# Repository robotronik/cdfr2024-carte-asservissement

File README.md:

# Carte d'asservissement Robotronik CDFR 2024

Projet Kicad qui a pour but de faire l'asservissement de la base roulante.

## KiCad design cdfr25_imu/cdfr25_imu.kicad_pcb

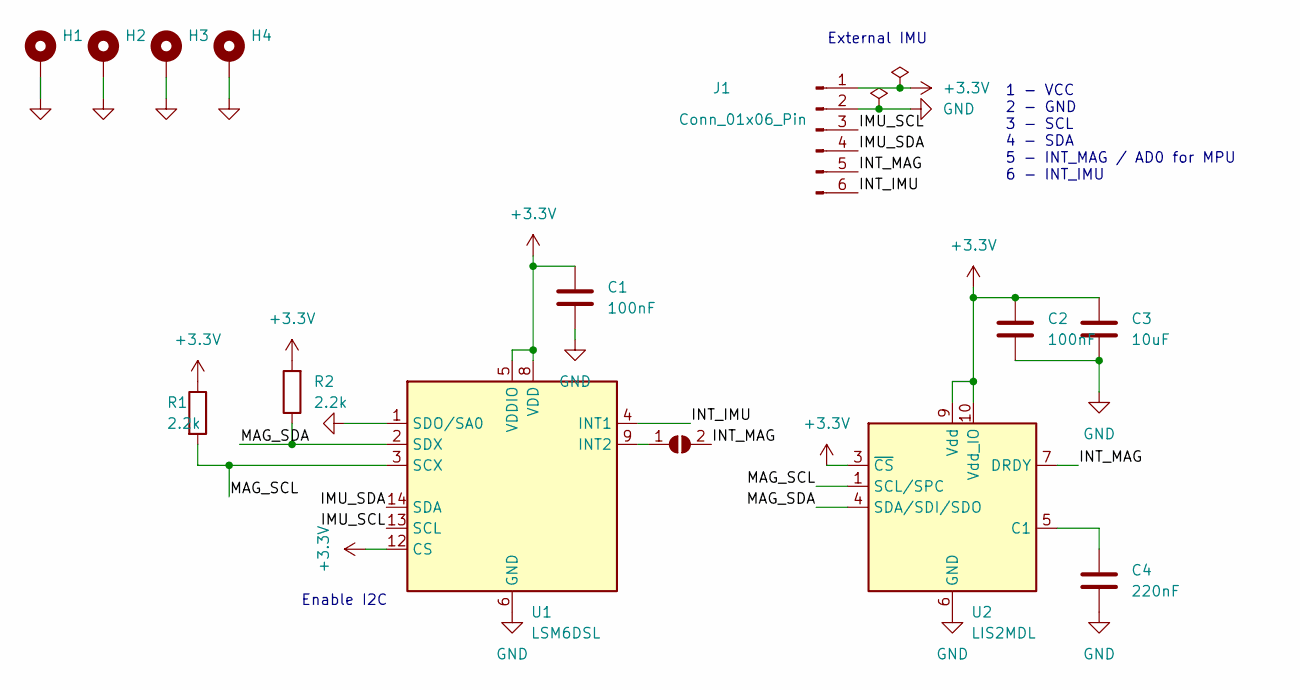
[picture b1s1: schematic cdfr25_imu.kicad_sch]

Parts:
C1, C2: 100nF; C_0805_2012Metric_Pad1.18x1.45mm_HandSolder
C3: 10uF; C_0805_2012Metric_Pad1.18x1.45mm_HandSolder
C4: 220nF; C_0805_2012Metric_Pad1.18x1.45mm_HandSolder
H1, H2, H3, H4: MountingHole_Pad; MountingHole_2.2mm_M2_Pad_Via
J1: Conn_01x06_Pin; PinHeader_1x06_P2.54mm_Vertical
JP1: SolderJumper_2_Open; SolderJumper-2_P1.3mm_Open_TrianglePad1.0x1.5mm
R1, R2: 2.2k; R_0805_2012Metric_Pad1.20x1.40mm_HandSolder
U1: LSM6DSL; LGA-14_3x2.5mm_P0.5mm_LayoutBorder3x4y
U2: LIS2MDL; LGA-12_2x2mm_P0.5mm

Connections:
+3.3V: C1.2, C2.2, C3.2, J1.1, R1.1, R2.2, U1.5 (VDDIO), U1.8 (VDD), U1.12 (CS), U2.3 (~CS), U2.9 (Vdd), U2.10 (Vdd_IO)
/IMU_SCL: J1.3, U1.13 (SCL)
/IMU_SDA: J1.4, U1.14 (SDA)
/INT_IMU: J1.6, U1.4 (INT1)
/INT_MAG: J1.5, JP1.2 (B), U2.7 (DRDY)
/MAG_SCL: R1.2, U1.3 (SCX), U2.1 (SCL/SPC)
/MAG_SDA: R2.1, U1.2 (SDX), U2.4 (SDA/SDI/SDO)
GND: C1.1, C2.1, C3.1, C4.1, H1.1, H2.1, H3.1, H4.1, J1.2, U1.1 (SDO/SA0), U1.6 (GND), U1.7 (GND), U2.6 (GND), U2.8 (GND)
unnamed: JP1.1 (A), U1.9 (INT2)
unnamed: C4.2, U2.5 (C1)

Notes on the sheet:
External IMU
Enable I2C
1 - VCC 2 - GND 3 - SCL 4 - SDA 5 - INT_MAG / AD0 for MPU 6 - INT_IMU

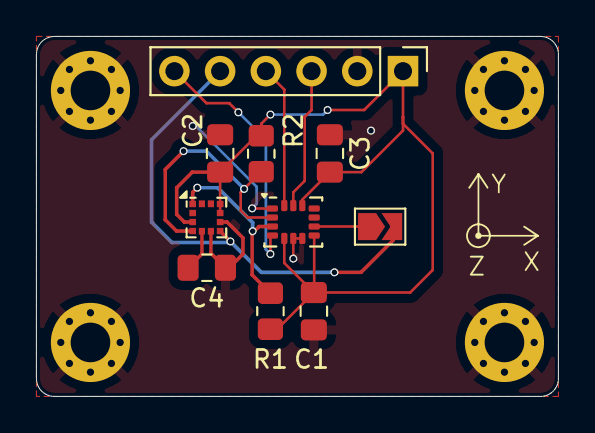
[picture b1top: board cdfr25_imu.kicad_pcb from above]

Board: 2 copper layers, 29.0 x 20.0 mm, 14 parts (0 on the bottom side), 10 nets.

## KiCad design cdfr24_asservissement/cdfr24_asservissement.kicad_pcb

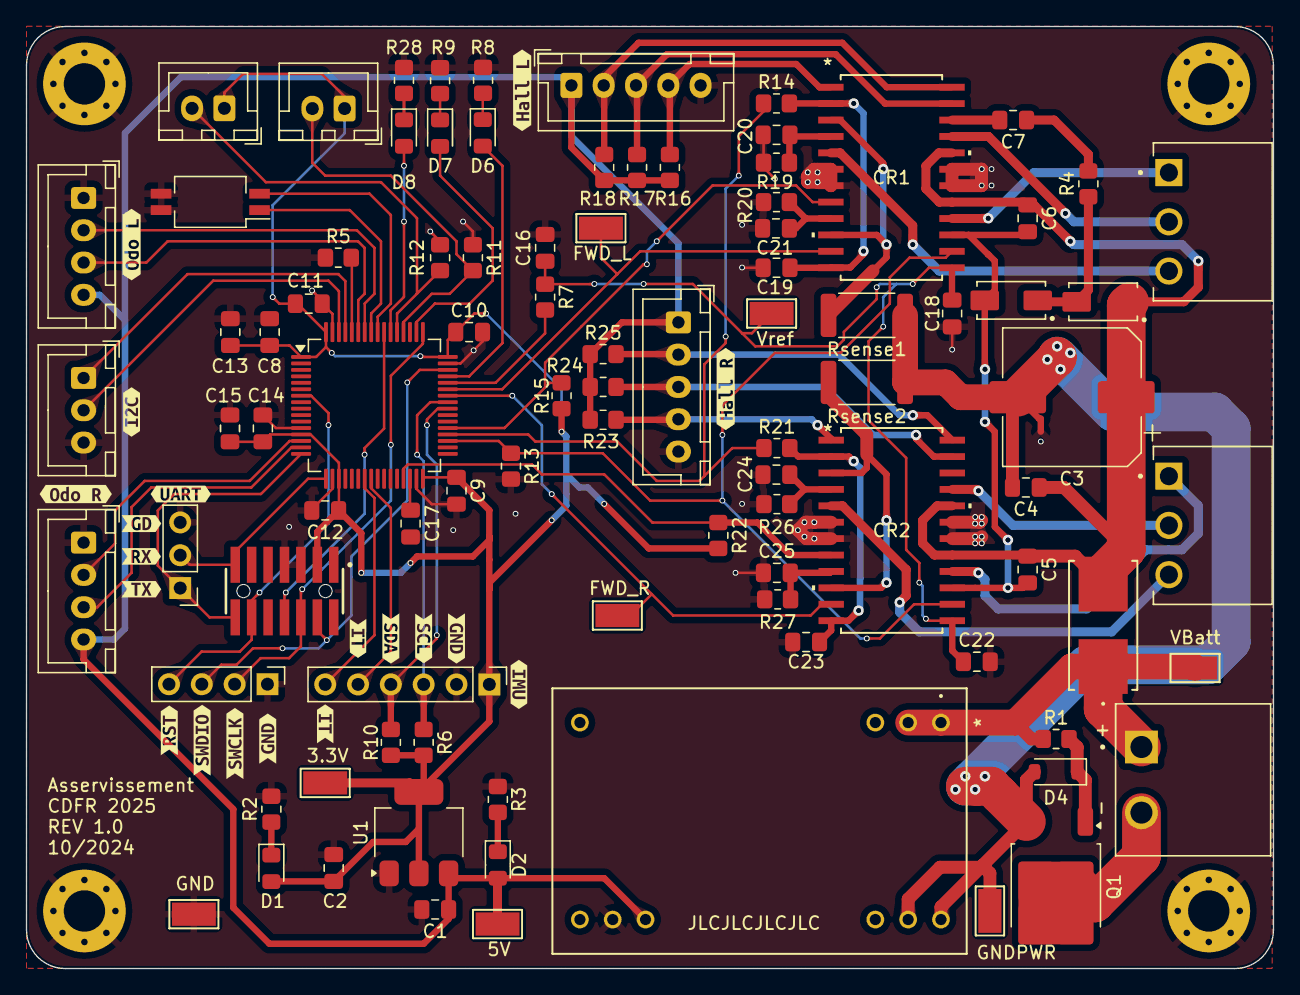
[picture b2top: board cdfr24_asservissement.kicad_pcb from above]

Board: 2 copper layers, 96.5 x 72.9 mm, 117 parts (0 on the bottom side), 70 nets.

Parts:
C1, C8, C9, C10, C11, C12: 100nF; C_0805_2012Metric_Pad1.18x1.45mm_HandSolder
C2, C13: 10uF; C_0805_2012Metric_Pad1.18x1.45mm_HandSolder
C3: 220u; CP_Elec_10x10.5
C4, C5, C6, C18, C22: 100n; C_0805_2012Metric_Pad1.18x1.45mm_HandSolder
C7: 10n; C_0805_2012Metric_Pad1.18x1.45mm_HandSolder
C14, C21, C25: 10nF; C_0805_2012Metric_Pad1.18x1.45mm_HandSolder
C15: 1uF; C_0805_2012Metric_Pad1.18x1.45mm_HandSolder
C16: ...; C_0805_2012Metric_Pad1.18x1.45mm_HandSolder
C17: 4.7uF; C_0805_2012Metric_Pad1.18x1.45mm_HandSolder
C19, C23: 5.6n; C_0805_2012Metric_Pad1.18x1.45mm_HandSolder
C20, C24: 1nF; C_0805_2012Metric_Pad1.18x1.45mm_HandSolder
CR1, CR2: L6235D; SO-24_STM
D1, D2, D6, D7, D8: LED; LED_0805_2012Metric_Pad1.15x1.40mm_HandSolder
D3, D5: D_Filled; DIOM505270X240
D4: D_Zener; D_SOD-123
F1: 01550900M; FUSE_01550900M_LTF
H1, H2, H3, H4: MountingHole_Pad; MountingHole_3.2mm_M3_Pad_Via
J1: Connecteur batterie; CUI_TBP01R1-508-02BE
J2, J6: Conn_01x05; JST_XH_B5B-XH-A_1x05_P2.50mm_Vertical
J3, J8: Conn_01x03; CUI_TBP02R1-381-03BE
J4: Conn_01x06_Pin; PinHeader_1x06_P2.54mm_Vertical
J5: Conn_ST_STDC14; SAMTEC_FTSH-107-01-L-DV-K-A
J7: Connecteur Programmation; PinHeader_1x04_P2.54mm_Vertical
J9, J11: Connecteur Odométrie; JST_XH_B4B-XH-A_1x04_P2.50mm_Vertical
J10: Conn_01x03; PinHeader_1x03_P2.54mm_Vertical
J12: Conn_01x03; JST_XH_B3B-XH-A_1x03_P2.50mm_Vertical
J13, J14: Conn_01x02; JST_XH_B2B-XH-A_1x02_P2.50mm_Vertical
NT1: NetTie_2; NetTie-2_SMD_Pad0.5mm
Q1: Q_NMOS_GDS; TO-252-2
R1: 56k; R_0805_2012Metric_Pad1.20x1.40mm_HandSolder
R2, R3: 150; R_0805_2012Metric_Pad1.20x1.40mm_HandSolder
R4: 100; R_0805_2012Metric_Pad1.20x1.40mm_HandSolder
R5, R11, R12, R13, R15, R16, R17, R18, R22, R23, R24, R25: 10k; R_0805_2012Metric_Pad1.20x1.40mm_HandSolder
R6, R10: 2.2k; R_0805_2012Metric_Pad1.20x1.40mm_HandSolder
R7: ...; R_0805_2012Metric_Pad1.20x1.40mm_HandSolder
R8, R9, R28: 220; R_0805_2012Metric_Pad1.20x1.40mm_HandSolder
R14, R21: 100k; R_0805_2012Metric_Pad1.20x1.40mm_HandSolder
R19, R26: 33k; R_0805_2012Metric_Pad1.20x1.40mm_HandSolder
R20, R27: 47k; R_0805_2012Metric_Pad1.20x1.40mm_HandSolder
Rsense1, Rsense2: 0.15; R_2512_6332Metric
SW1: SW_DIP_x02; SW_DIP_SPSTx02_Slide_Copal_CHS-02B_W7.62mm_P1.27mm
TP1, TP2, TP3, TP4, TP5, TP6, TP7, TP8: TestPoint; TestPoint_Keystone_5015_Micro-Minature
U1: LD1117S33TR_SOT223; SOT-223-3_TabPin2
U2: TVN 5-2411WI; TVN_5WI_SINGLE_TRP
U3: STM32F401RCTx; LQFP-64_10x10mm_P0.5mm
kibuzzard-670C1B62: G***; kibuzzard-670C1B62
kibuzzard-670C1B77: G***; kibuzzard-670C1B77
kibuzzard-670C1BB6: G***; kibuzzard-670C1BB6
kibuzzard-670C1BE0: G***; kibuzzard-670C1BE0
kibuzzard-670C1C38: G***; kibuzzard-670C1C38
kibuzzard-670C1C44: G***; kibuzzard-670C1C44
kibuzzard-670C1C88: G***; kibuzzard-670C1C88
kibuzzard-670C1CA4: G***; kibuzzard-670C1CA4
kibuzzard-670C1CC0: G***; kibuzzard-670C1CC0
kibuzzard-670C1CCE: G***; kibuzzard-670C1CCE
kibuzzard-670C1CDC: G***; kibuzzard-670C1CDC
kibuzzard-670C1D0C: G***; kibuzzard-670C1D0C
kibuzzard-670C1D6D: G***; kibuzzard-670C1D6D
kibuzzard-670C1D22: G***; kibuzzard-670C1D22
kibuzzard-670C1D36: G***; kibuzzard-670C1D36
kibuzzard-670C1D87: G***; kibuzzard-670C1D87
kibuzzard-670C1D91: G***; kibuzzard-670C1D91
kibuzzard-670C1DC2: G***; kibuzzard-670C1DC2
kibuzzard-670C1DD5: G***; kibuzzard-670C1DD5

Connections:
+3.3V: C2.1, C8.1, C9.1, C10.1, C11.1, C12.1, C13.1, C14.1, C15.1, D1.2 (A), J4.1, J5.3 (VCC), J13.1, J14.1, R6.2, R10.2, R15.2, R22.2, TP1.1, U1.2 (VO), U3.1 (VBAT), U3.13 (VREF+), U3.19 (VDD), U3.32 (VDD), U3.48 (VDD), U3.64 (VDD)
+5V: C1.1, D2.2 (A), J2.1, J6.1, J9.4, J11.4, R16.1, R17.1, R18.1, R23.1, R24.1, R25.1, TP4.1, U1.3 (VI), U2.15 (+VOUT)
+BATT: F1.1, J1.1, R1.1, TP2.1, U2.1 (+VIN(VCC)), U2.2 (+VIN(VCC))
/BRAKE_MOT: CR1.14 (BRAKE), CR2.14 (BRAKE), R13.2, U3.35 (PB14)
/EN_MOT: R14.1, R21.1, U3.36 (PB15)
/FWD_L: CR1.11 (FWD/REV), TP6.1, U3.43 (PA10)
/FWD_R: CR2.11 (FWD/REV), TP8.1, U3.42 (PA9)
/I2C_CLK: J12.1, U3.61 (PB8)
/I2C_SDA: J12.2, U3.62 (PB9)
/IMU_SCL: J4.3, R6.1, U3.41 (PA8)
/IMU_SDA: J4.4, R10.1, U3.40 (PC9)
/INT_IMU: J4.6, U3.23 (PA7)
/INT_MAG: J4.5, U3.24 (PC4)
/RX: J5.13 (VCP_RX), J10.2, U3.17 (PA3)
/TACHO_L: CR1.8 (TACHO), R15.1, U3.37 (PC6)
/TACHO_R: CR2.8 (TACHO), R22.1, U3.29 (PB10)
/TX: J5.14 (VCP_TX), J10.1, U3.16 (PA2)
/Vboot: C5.2, C6.2, CR1.15 (VBOOT), CR2.15 (VBOOT), D5.1 (K)
/Vcp_L: C7.2, CR1.22 (VCP)
/Vref_DAC: C16.1, C18.1, C22.1, CR1.13 (VREF), CR2.13 (VREF), R7.1, TP7.1
/Vsab: C3.1, C4.1, C5.1, C6.1, CR1.17 (VSB), CR1.20 (VSA), CR2.17 (VSB), CR2.20 (VSA), D3.2 (A), F1.2
/left_driver/H1: CR1.1 (H1), J2.4, R16.2
/left_driver/H2: CR1.23 (H2), J2.3, R17.2
/left_driver/H3: CR1.24 (H3), J2.2, R18.2
/left_driver/OUT1: CR1.5 (OUT1), J3.3
/left_driver/OUT2: CR1.21 (OUT2), J3.2
/left_driver/OUT3: CR1.16 (OUT3), J3.1
/right_driver/H1: CR2.1 (H1), J6.4, R23.2
/right_driver/H2: CR2.23 (H2), J6.3, R24.2
/right_driver/H3: CR2.24 (H3), J6.2, R25.2
/right_driver/OUT1: CR2.5 (OUT1), J8.3
/right_driver/OUT2: CR2.21 (OUT2), J8.2
/right_driver/OUT3: CR2.16 (OUT3), J8.1
GND: C1.2, C2.2, C8.2, C9.2, C10.2, C11.2, C12.2, C13.2, C14.2, C15.2, C16.2, C17.2, C18.2, C19.1, C20.1, C21.1, C22.2, C23.1, C24.1, C25.1, CR1.6 (GND), CR1.7 (GND), CR1.18 (GND), CR1.19 (GND), CR2.6 (GND), CR2.7 (GND), CR2.18 (GND), CR2.19 (GND), H1.1, H2.1, H3.1, H4.1, J2.5, J4.2, J5.5 (GND), J5.7 (GND), J6.5, J7.1, J9.1, J10.3, J11.1, J12.3, NT1.2, R2.2, R3.2, R5.1, R8.2, R9.2, R11.1, R12.1, R13.1, R19.1, R20.1, R26.1, R27.1, R28.2, SW1.3, SW1.4, TP5.1, U1.1 (GND), U2.14 (-VOUT), U3.12 (VSSA), U3.18 (VSS), U3.31 (VSS), U3.47 (VSS), U3.63 (VSS)
GNDPWR: C3.2, C4.2, D4.2 (A), NT1.1, Q1.3 (S), Rsense1.1, Rsense2.1, TP3.1, U2.23 (-VIN(GND)), U2.24 (-VIN(GND))
unnamed: C7.1, R4.2
unnamed: C19.2, CR1.2 (DIAG), CR1.12 (EN), R14.2
unnamed: C20.2, CR1.4 (RCOFF), R19.2
unnamed: C21.2, CR1.9 (RCPULSE), R20.2
unnamed: CR1.3 (SENSEA), CR1.10 (SENSEB), Rsense1.2
unnamed: C23.2, CR2.2 (DIAG), CR2.12 (EN), R21.2
unnamed: C24.2, CR2.4 (RCOFF), R26.2
unnamed: C25.2, CR2.9 (RCPULSE), R27.2
unnamed: CR2.3 (SENSEA), CR2.10 (SENSEB), Rsense2.2
unnamed: D1.1 (K), R2.1
unnamed: D2.1 (K), R3.1
unnamed: D3.1 (K), D5.2 (A), R4.1
unnamed: D4.1 (K), Q1.1 (G), R1.2
unnamed: D6.2 (A), U3.45 (PA12)
unnamed: D6.1 (K), R8.1
unnamed: D7.2 (A), U3.50 (PA15)
unnamed: D7.1 (K), R9.1
unnamed: D8.2 (A), U3.54 (PD2)
unnamed: D8.1 (K), R28.1
unnamed: J1.2, Q1.2 (D)
unnamed: J9.2, U3.14 (PA0)
unnamed: J9.3, U3.15 (PA1)
unnamed: J11.2, U3.58 (PB6)
unnamed: J11.3, U3.59 (PB7)
unnamed: J13.2, R11.2, U3.52 (PC11)
unnamed: J14.2, R12.2, U3.53 (PC12)
unnamed: R5.2, U3.60 (BOOT0)
unnamed: R7.2, U3.44 (PA11)
unnamed: SW1.2, U3.56 (PB4)
unnamed: SW1.1, U3.57 (PB5)
unnamed: C17.1, U3.30 (VCAP1)
RST: J5.12 (~RST), J7.4, U3.7 (NRST)
SWCLK: J5.6 (JCLK/SWCLK), J7.2, U3.49 (PA14)
SWDIO: J5.4 (JTMS/SWDIO), J7.3, U3.46 (PA13)
SWO: J5.8 (JTDO/SWO), U3.55 (PB3)

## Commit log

2023-11-01 Create project
2023-11-12 First draft of schematic
2023-11-18 change EXTI and boot0 pin connection
2023-11-18 new connecteur stlink
2023-11-19 Add footprints
2023-11-24 Place PCB components
2023-11-27 Route PCB, still need to resolve DRC errors
2023-11-28 Resolve some errors
2023-11-30 Fixed errors
2023-11-30 Remove lock
2023-12-07 correction Routage
2024-01-04 Update via size
2024-09-04 Update gitignore
2024-09-08 Add new components
2024-09-09 Change 5v to 3.3v regulator to ST product
2024-09-10 Realign elements to grid
2024-09-12 Combine charge pump
2024-09-15 Change STM32 pins
2024-09-17 Add low pass filter
2024-09-17 Add LEDs and remove capacitor
2024-09-21 Fix warnings, add DIP switches
2024-09-22 Place components
2024-09-24 Improve placement
2024-09-24 Remove gitginore files
2024-09-25 Start routing
2024-09-29 Finish routing
2024-09-29 Add silkscreen and logo
2024-10-13 Add text on PCB
2024-10-14 Add IMU schematic
2024-10-14 Route IMU
2024-10-15 Fix clearance problem
2024-10-16 Add marking
